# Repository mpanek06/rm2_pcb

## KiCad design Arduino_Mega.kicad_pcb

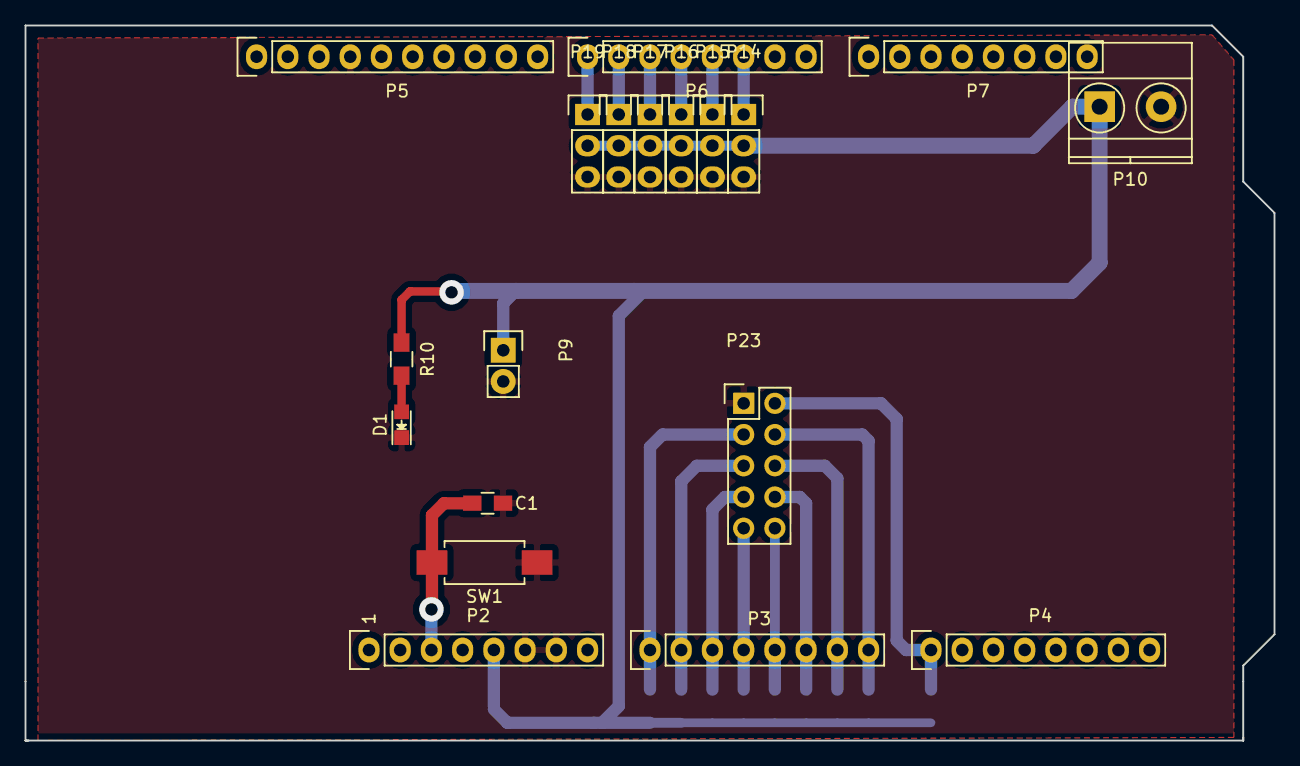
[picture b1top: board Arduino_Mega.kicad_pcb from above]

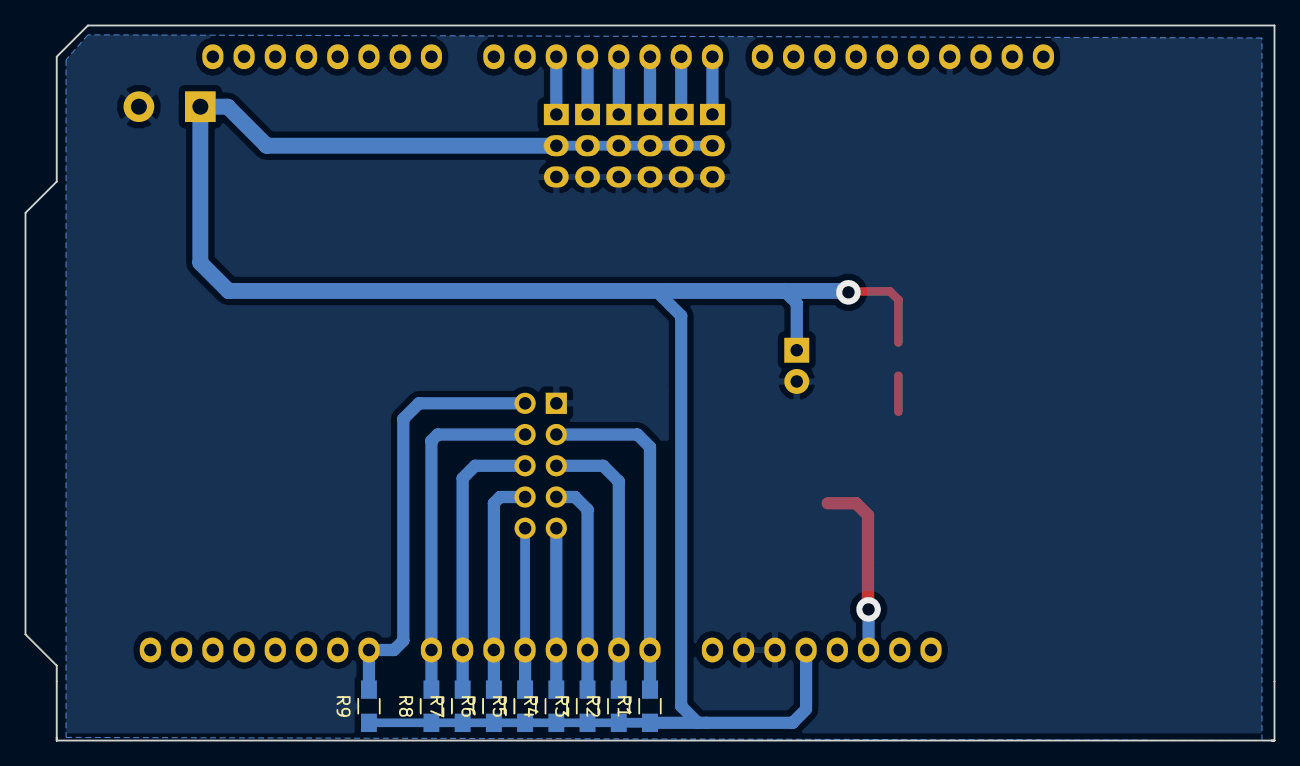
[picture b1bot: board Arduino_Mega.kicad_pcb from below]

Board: 2 copper layers, 101.6 x 58.2 mm, 28 parts (9 on the bottom side), 19 nets.

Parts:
C1: 100nF; C_0805_HandSoldering
D1: POWER_LED; LED_0805
P2: Power; Socket_Strip_Arduino_1x08
P3, P4: Analog; Socket_Strip_Arduino_1x08
P5: PWM; Socket_Strip_Arduino_1x10
P6: PWM; Socket_Strip_Arduino_1x08
P7: Communication; Socket_Strip_Arduino_1x08
P9: PWR_OUT; Socket_Strip_Straight_1x02
P10: CONN_2; TerminalBlock_Pheonix_MKDS1.5-2pol
P14: SERVO_OUT_0; Pin_Header_Straight_1x03
P15: SERVO_OUT_1; Pin_Header_Straight_1x03
P16: SERVO_OUT_2; Pin_Header_Straight_1x03
P17: SERVO_OUT_3; Pin_Header_Straight_1x03
P18: SERVO_OUT_4; Pin_Header_Straight_1x03
P19: SERVO_OUT_5; Pin_Header_Straight_1x03
P23: SENOSRS_IN; Pin_Header_Straight_2x05
R1, R2, R3, R4, R5, R6, R7, R8, R9: 10k; R_0805_HandSoldering
R10: 150; R_0805_HandSoldering
SW1: RST; SW_SPST_REED_CT05-XXXX-G1

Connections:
+5V: P2.5, P9.1, P10.1, P14.2, P15.2, P16.2, P17.2, P18.2, P19.2, R1.1, R2.1, R3.1, R4.1, R5.1, R6.1, R7.1, R8.1, R9.1, R10.1
/Arduino_CON/PWM0: P6.6, P14.1
/Arduino_CON/PWM1: P6.5, P15.1
/Arduino_CON/PWM2: P6.4, P16.1
/Arduino_CON/PWM3: P6.3, P17.1
/Arduino_CON/PWM4: P6.2, P18.1
/Arduino_CON/PWM5: P6.1, P19.1
/VoltageDivider/ADC0: P3.1, P23.3, R1.2
/VoltageDivider/ADC1: P3.2, P23.5, R2.2
/VoltageDivider/ADC2: P3.3, P23.7, R3.2
/VoltageDivider/ADC3: P3.4, P23.9, R4.2
/VoltageDivider/ADC4: P3.5, P23.10, R5.2
/VoltageDivider/ADC5: P3.6, P23.8, R6.2
/VoltageDivider/ADC6: P3.7, P23.6, R7.2
/VoltageDivider/ADC7: P3.8, P23.4, R8.2
/VoltageDivider/ADC8: P4.1, P23.2, R9.2
GND: C1.1, D1.1, P2.6, P2.7, P5.4, P9.2, P10.2, P14.3, P15.3, P16.3, P17.3, P18.3, P19.3, P23.1, SW1.2
unnamed: D1.2, R10.2
RST: C1.2, P2.3, SW1.1

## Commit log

2016-10-11 init commit
2016-10-11 Initial schema
2016-10-11 Netlist and PCB generated
2016-10-12 PCB rev1.0
2016-10-12 PCB rev1.0 part @
2016-10-13 pcb rev2
2016-10-15 Jumper removed, pdf generated
